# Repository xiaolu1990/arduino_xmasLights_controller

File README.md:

# arduino_xmasLights_controller
simple WS2812B LED strip controller based on Arduino platform. 

**Features:**

1. Solid color control with dimming function.
2. Several pre-built led patterns such as twinkle effect, breathing effect, chasing effect, etc.
3. Play Christmas songs together with LED sparkling effect.

**Hardware:**

this is a small project that utilizes an Arduino Nano to control any typical addressable 5V LED strip using WS2812. The parts needed are:
- Arduino Nano x 1 (main controller)
- Rotary Encoder x 1 (menu control knob)
- Rotary potentiometer x 1 (led dimming control)
- 0.91" OLED display x 1 
- Buzzer x 1
- Some other passive compoenents, see in schematic.

I have made the parts together on a perf board and upload the code in this repo, and it works nicely :) 

Check the [Demo on Youtube](https://www.youtube.com/shorts/xX7Cnof2Gqg)

I have also designed a PCB in Kicad for this project, details inside `hardware/` folder.

**Firmware:**

The source code and platformIO config file for the demo video are located under folder `firmware/`.

Merry Christmas and happy new year 2023,  
Zhangshun

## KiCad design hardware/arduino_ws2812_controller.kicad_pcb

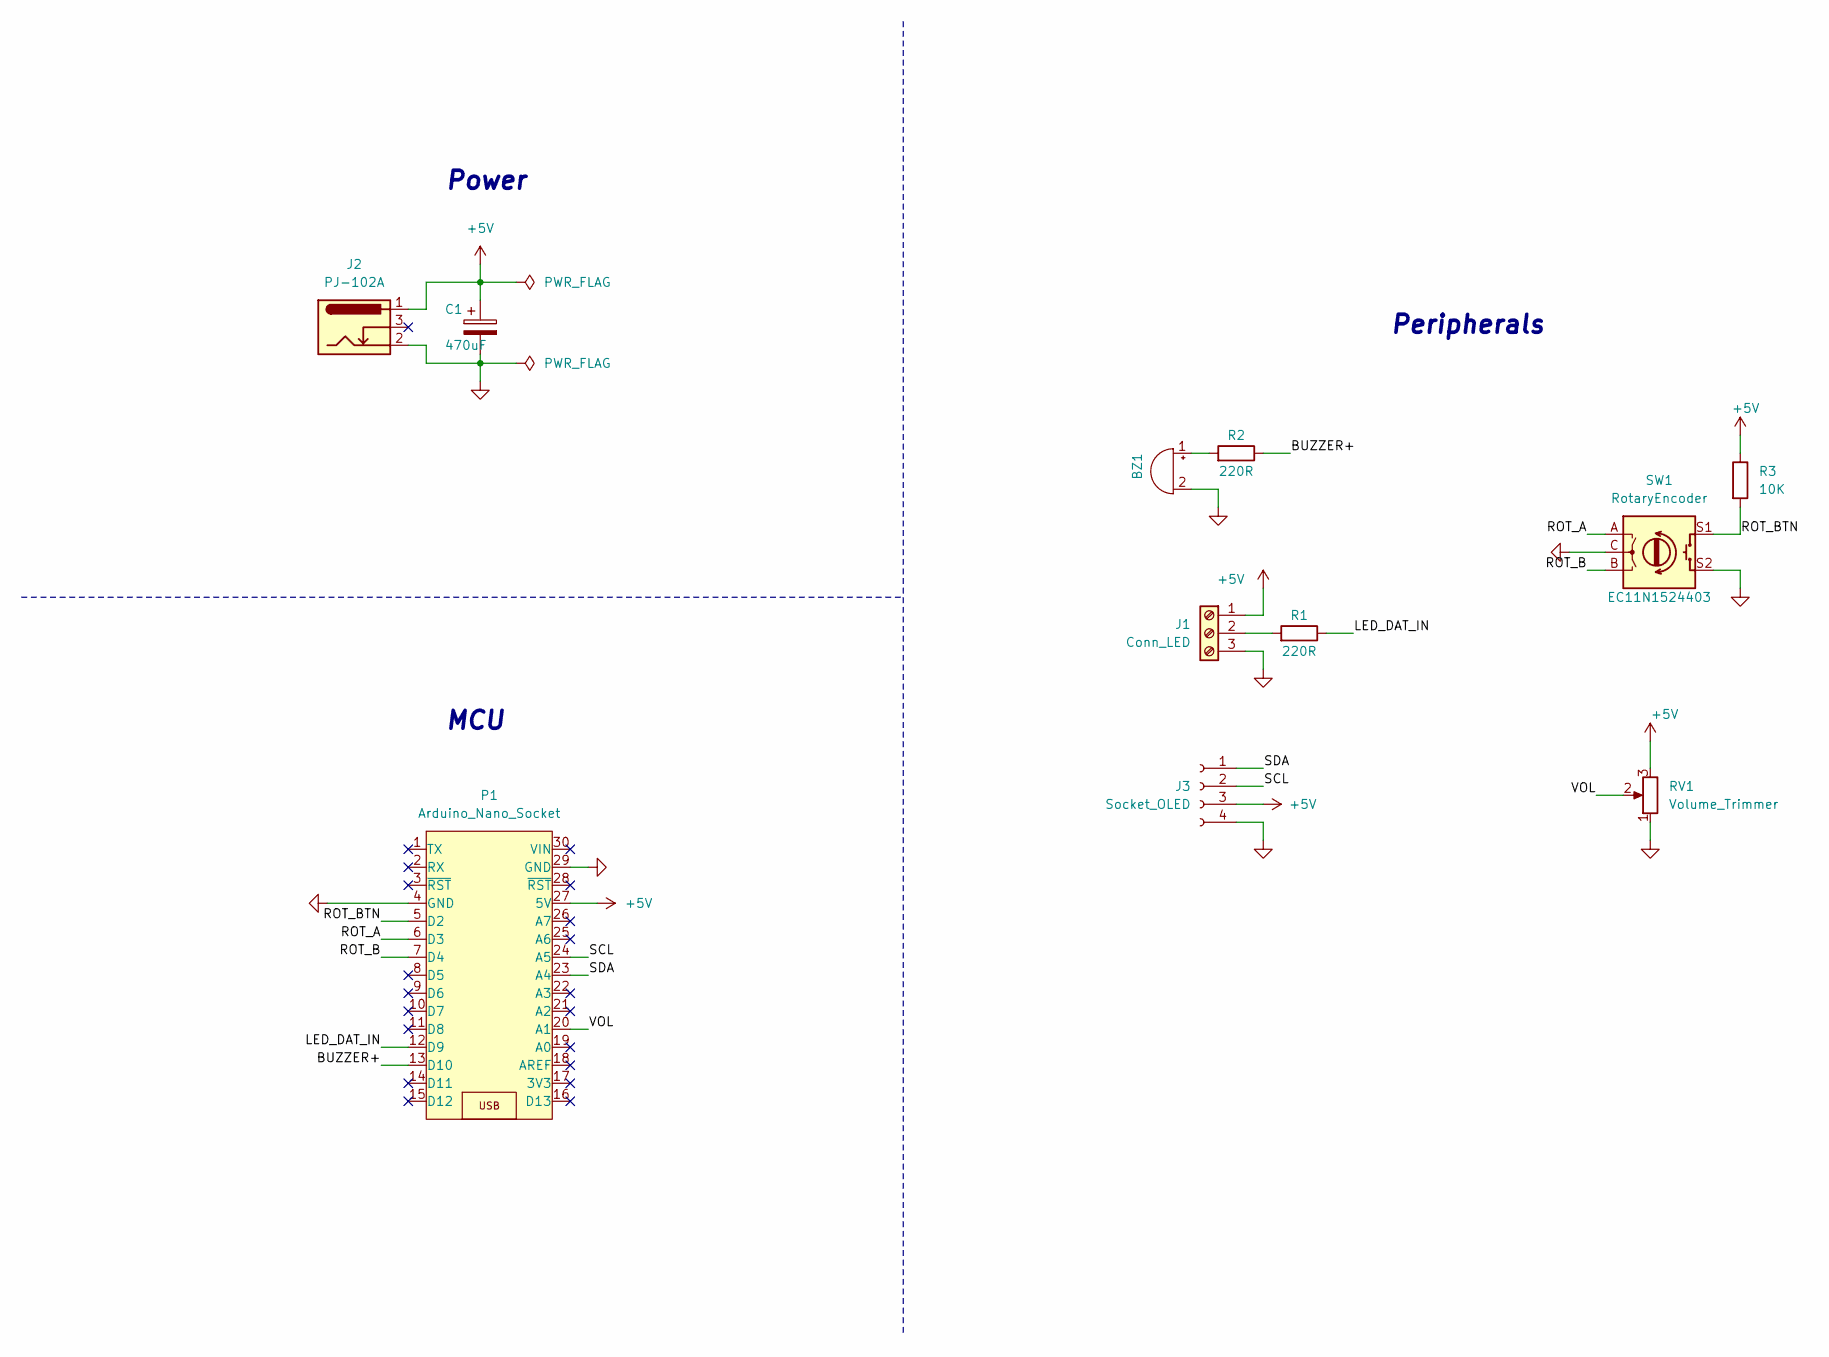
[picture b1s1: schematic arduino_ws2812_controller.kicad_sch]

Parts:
BZ1: Buzzer; Buzzer_12x9.5RM7.6
C1: 470uF; CP_Radial_D4.0mm_P2.00mm
J1: Conn_LED; TerminalBlock_Phoenix_MKDS-1,5-3_1x03_P5.00mm_Horizontal
J2: PJ-102A; BarrelJack_CUI_PJ-102AH_Horizontal; MPN PJ-102A
J3: Socket_OLED; PinSocket_1x04_P2.54mm_Vertical
P1: Arduino_Nano_Socket
R1, R2: 220R; R_Axial_DIN0204_L3.6mm_D1.6mm_P5.08mm_Horizontal
R3: 10K; R_Axial_DIN0204_L3.6mm_D1.6mm_P5.08mm_Horizontal
RV1: Volume_Trimmer; Potentiometer_Alpha_RD901F-40-00D_Single_Vertical; MPN RD901F-40-15R1-B10K-00DL1
SW1: RotaryEncoder; RotaryEncoder_Alps_EC11E-Switch_Vertical_H20mm; MPN EC11N1524403

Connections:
+5V: C1.1, J1.1, J2.1, J3.3, P1.27 (5V), R3.1, RV1.3
/BUZZER+: P1.13 (D10), R2.1
/LED_DAT_IN: P1.12 (D9), R1.1
/ROT_A: P1.6 (D3), SW1.A
/ROT_B: P1.7 (D4), SW1.B
/ROT_BTN: P1.5 (D2), R3.2, SW1.S1
/SCL: J3.2, P1.24 (A5)
/SDA: J3.1, P1.23 (A4)
/VOL: P1.20 (A1), RV1.2
GND: BZ1.2 (+), C1.2, J1.3, J2.2, J3.4, P1.4 (GND), P1.29 (GND), RV1.1, SW1.C, SW1.S2
unnamed: J1.2, R1.2
unnamed: BZ1.1 (-), R2.2

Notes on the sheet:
Peripherals
MCU
Power

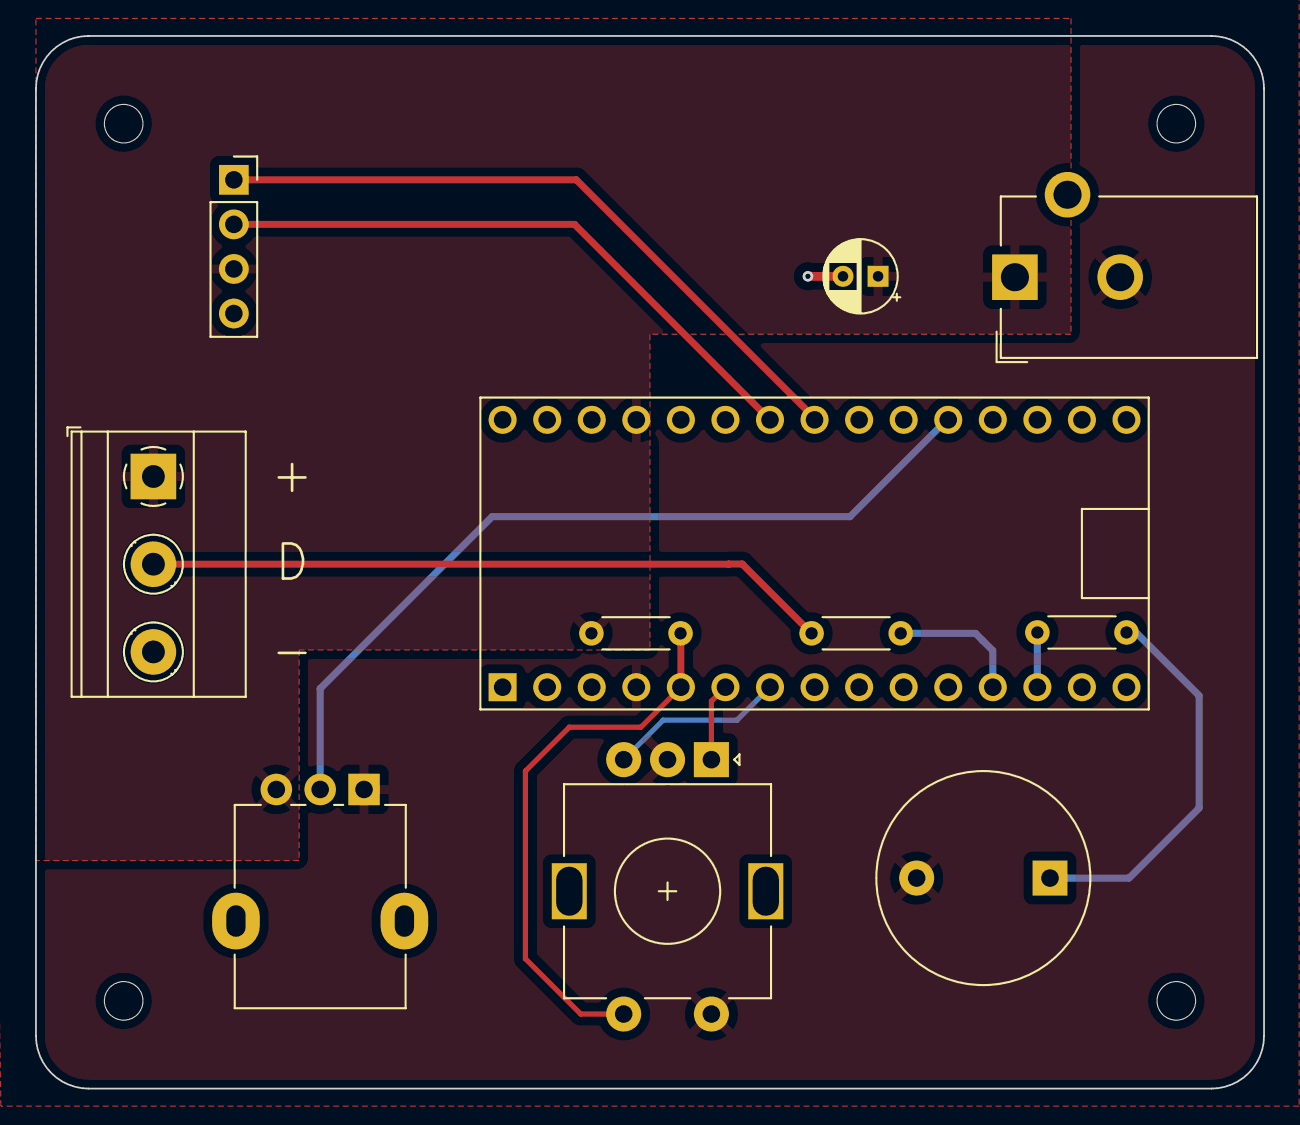
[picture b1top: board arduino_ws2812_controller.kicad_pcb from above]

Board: 2 copper layers, 70.0 x 60.0 mm, 11 parts (0 on the bottom side), 12 nets.

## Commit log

2022-12-25 update design files and firmware code
